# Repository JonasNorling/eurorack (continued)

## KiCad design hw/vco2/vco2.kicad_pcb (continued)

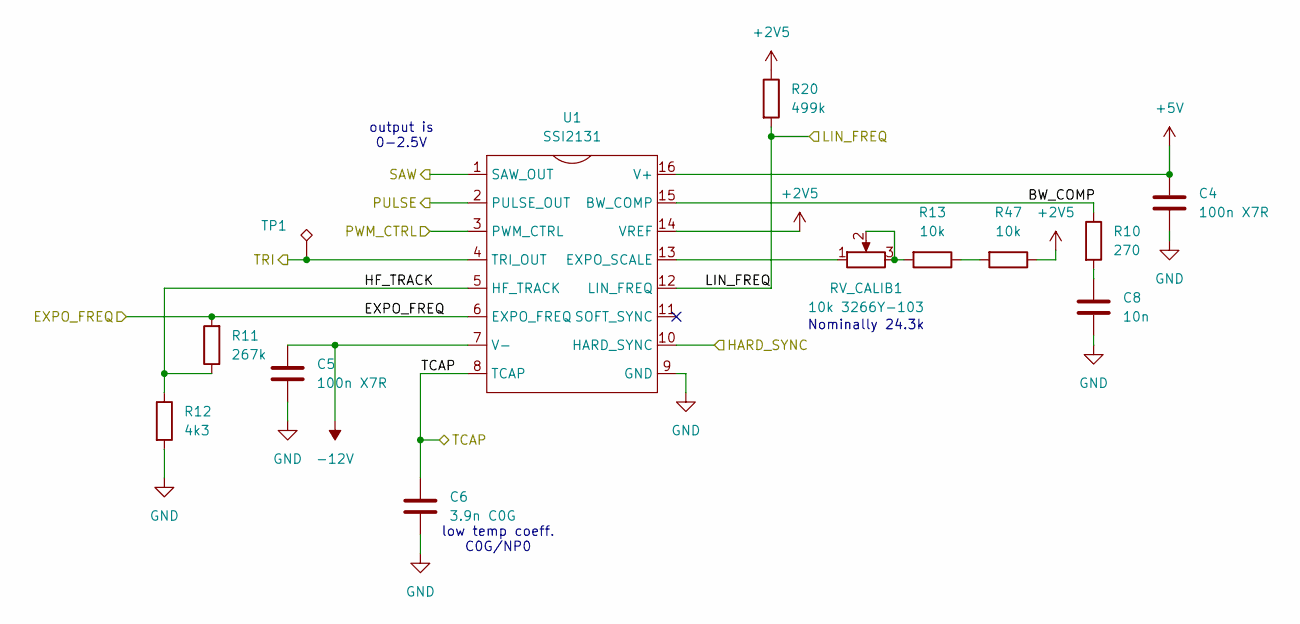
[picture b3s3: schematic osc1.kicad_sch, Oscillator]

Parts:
C4, C5: 100n X7R; C_0603_1608Metric
C6: 3.9n C0G; C_0603_1608Metric
C8: 10n; C_0603_1608Metric
R10: 270; R_0603_1608Metric
R11: 267k; R_0603_1608Metric
R12: 4k3; R_0603_1608Metric
R13, R47: 10k; R_0603_1608Metric
R20: 499k; R_0603_1608Metric
RV_CALIB1: 10k 3266Y-103; Potentiometer_Bourns_3266Y_Vertical
TP1: TestPoint_Alt; TP_0.9mm
U1: SSI2131; STC_SOP-16_3.9x9.9mm_P1.27mm; LCSC C9900051822

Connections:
+2V5: R20.1, R47.1, U1.14 (VREF); also elsewhere on the board
+5V: C4.1, U1.16 (V+); also elsewhere on the board
-12V: C5.1, U1.7 (V-); also elsewhere on the board
/EXPO_FREQ1: R11.2, U1.6 (EXPO_FREQ); also elsewhere on the board
/HARD_SYNC1: U1.10 (HARD_SYNC); also elsewhere on the board
/LIN_FREQ1: R20.2, U1.12 (LIN_FREQ); also elsewhere on the board
/Oscillator 1/BW_COMP: R10.1, U1.15 (BW_COMP)
/Oscillator 1/HF_TRACK: R11.1, R12.1, U1.5 (HF_TRACK)
/Oscillator 1/TCAP: C6.1, U1.8 (TCAP)
/PULSE1: U1.2 (PULSE_OUT); also elsewhere on the board
/PWM_CTRL1: U1.3 (PWM_CTRL); also elsewhere on the board
/SAW1: U1.1 (SAW_OUT); also elsewhere on the board
/TRI1: TP1.1, U1.4 (TRI_OUT); also elsewhere on the board
GND: C4.2, C5.2, C6.2, C8.2, R12.2, U1.9 (GND); also elsewhere on the board
unnamed: C8.1, R10.2
unnamed: R13.1, R47.2
unnamed: R13.2, RV_CALIB1.2, RV_CALIB1.3
unnamed: RV_CALIB1.1, U1.13 (EXPO_SCALE)

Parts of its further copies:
C24, C27: 100n X7R; C_0603_1608Metric
C25: 3.9n C0G; C_0603_1608Metric
C26: 10n; C_0603_1608Metric
R48, R66: 10k; R_0603_1608Metric
R63: 4k3; R_0603_1608Metric
R64: 267k; R_0603_1608Metric
R65: 499k; R_0603_1608Metric
R67: 270; R_0603_1608Metric
RV_CALIB2: 10k 3266Y-103; Potentiometer_Bourns_3266Y_Vertical
TP9: TestPoint_Alt; TP_0.9mm
U9: SSI2131; STC_SOP-16_3.9x9.9mm_P1.27mm; LCSC C9900051822

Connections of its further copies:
+2V5: R48.1, R65.1, U9.14 (VREF); also elsewhere on the board
+5V: C27.1, U9.16 (V+); also elsewhere on the board
-12V: C24.1, U9.7 (V-); also elsewhere on the board
/EXPO_FREQ2: R64.2, U9.6 (EXPO_FREQ); also elsewhere on the board
/HARD_SYNC2: U9.10 (HARD_SYNC); also elsewhere on the board
/Oscillator 2/BW_COMP: R67.1, U9.15 (BW_COMP)
/Oscillator 2/HF_TRACK: R63.1, R64.1, U9.5 (HF_TRACK)
/Oscillator 2/LIN_FREQ: R65.2, U9.12 (LIN_FREQ)
/PULSE2: U9.2 (PULSE_OUT); also elsewhere on the board
/PWM_CTRL2: U9.3 (PWM_CTRL); also elsewhere on the board
/SAW2: U9.1 (SAW_OUT); also elsewhere on the board
/TCAP2: C25.1, U9.8 (TCAP); also elsewhere on the board
/TRI2: TP9.1, U9.4 (TRI_OUT); also elsewhere on the board
GND: C24.2, C25.2, C26.2, C27.2, R63.2, U9.9 (GND); also elsewhere on the board
unnamed: C26.1, R67.2
unnamed: R48.2, R66.1
unnamed: R66.2, RV_CALIB2.2, RV_CALIB2.3
unnamed: RV_CALIB2.1, U9.13 (EXPO_SCALE)

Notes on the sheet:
Nominally 24.3k
low temp coeff. C0G/NP0
output is 0-2.5V

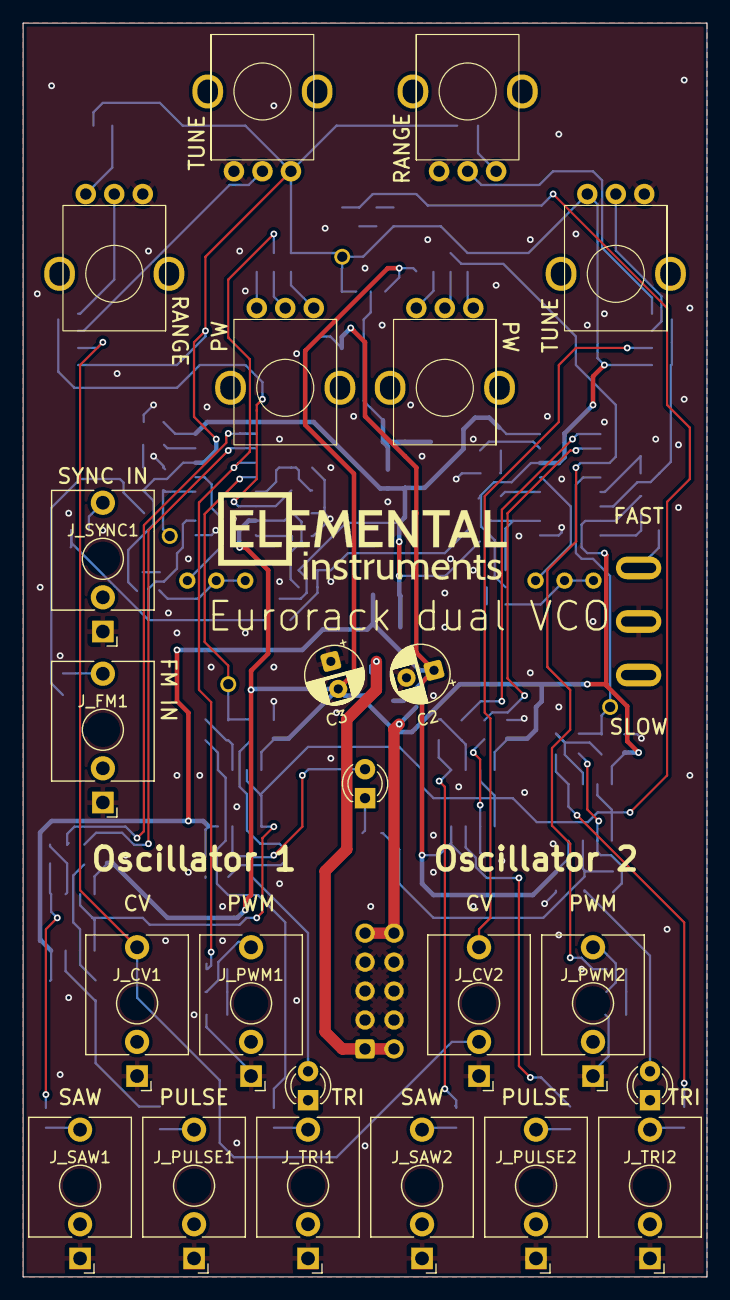
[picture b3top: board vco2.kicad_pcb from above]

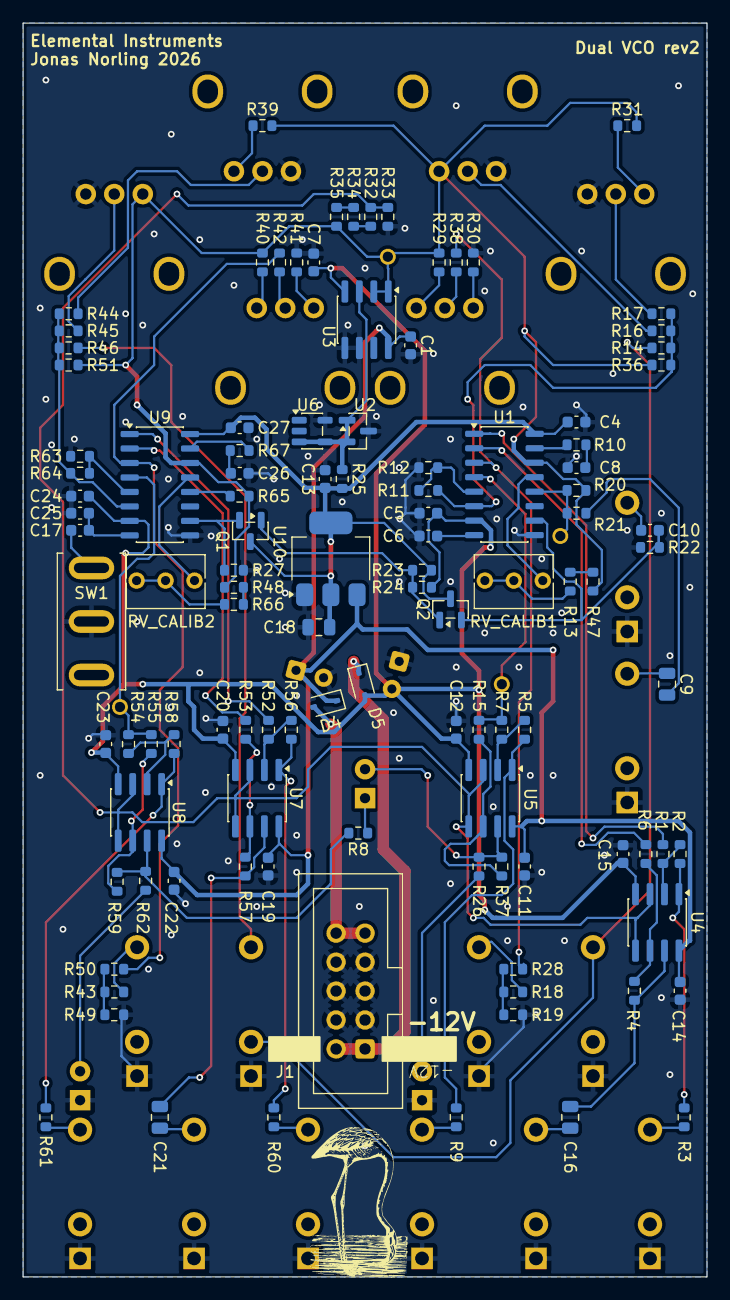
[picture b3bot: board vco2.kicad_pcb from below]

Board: 2 copper layers, 60.0 x 110.0 mm, 137 parts (114 on the bottom side), 87 nets.

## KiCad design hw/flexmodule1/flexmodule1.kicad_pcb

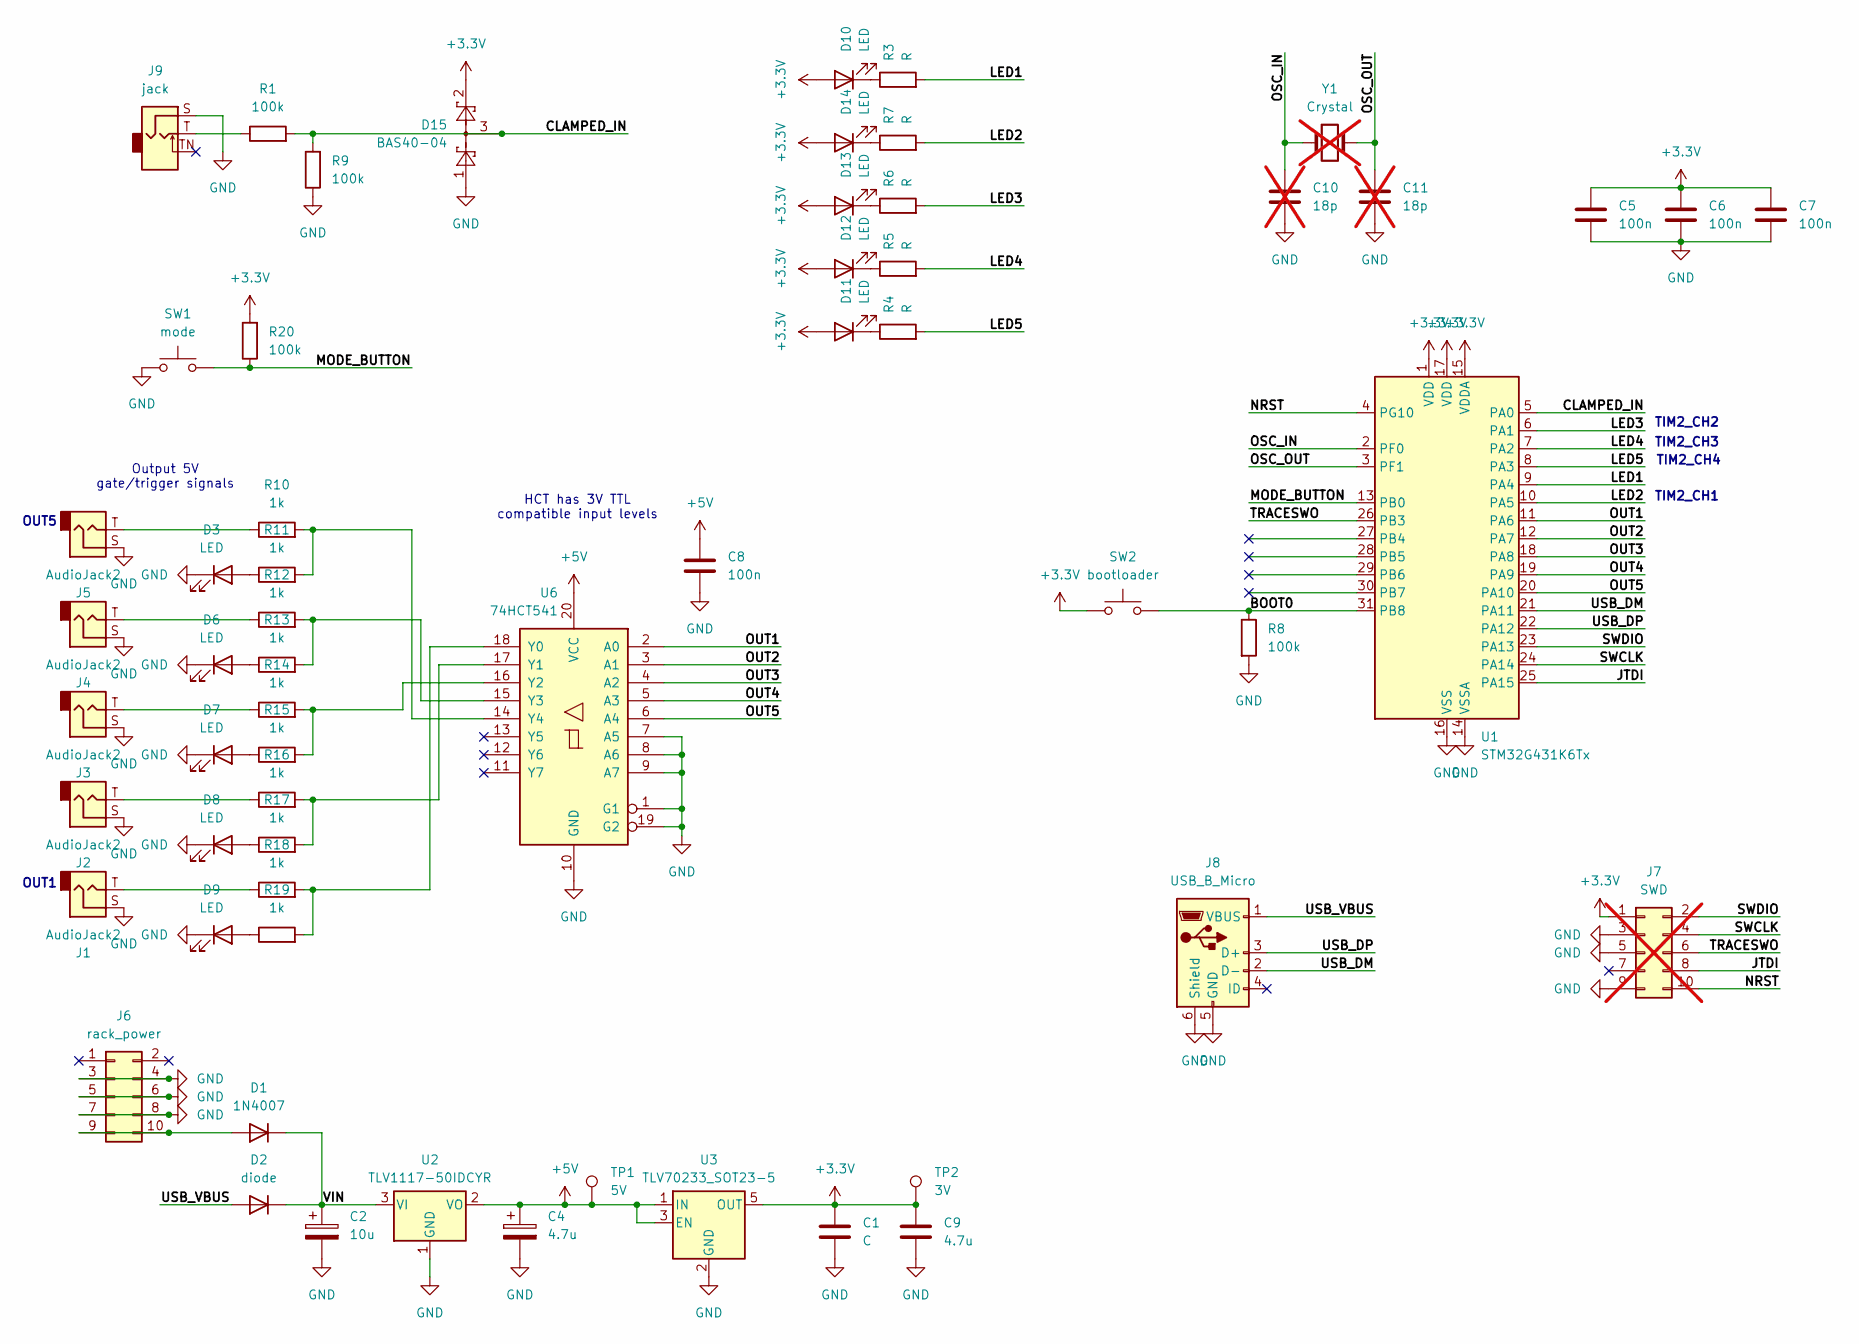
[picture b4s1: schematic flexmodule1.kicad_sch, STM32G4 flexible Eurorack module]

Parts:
C1: C; C_0603_1608Metric_Pad1.08x0.95mm_HandSolder
C2: 10u; CP_Radial_D5.0mm_P2.50mm
C4, C9: 4.7u; C_1206_3216Metric_Pad1.33x1.80mm_HandSolder
C5, C6, C7, C8: 100n; C_0603_1608Metric_Pad1.08x0.95mm_HandSolder
C10, C11: 18p; C_0603_1608Metric_Pad1.08x0.95mm_HandSolder; not fitted
D1: 1N4007; D_SOD-323
D2: diode; D_SOD-323
D3, D6, D7, D8, D9, D10, D11, D12, D13, D14: LED; LED_D3.0mm
D15: BAS40-04; SOT-23
J1, J2, J3, J4, J5: AudioJack2; Jack_3.5mm_QingPu_WQP-PJ398SM_Vertical_CircularHoles
J6: rack_power; IDC-Header_2x05_P2.54mm_Vertical
J7: SWD; PinHeader_2x05_P1.27mm_Vertical; not fitted
J8: USB_B_Micro; USB_Micro-B_Amphenol_10118193-0001LF_Horizontal
J9: jack; Jack_3.5mm_QingPu_WQP-PJ398SM_Vertical_CircularHoles
R1, R8, R9, R20: 100k; R_0603_1608Metric_Pad0.98x0.95mm_HandSolder
R3, R4, R5, R6, R7: R; R_0603_1608Metric_Pad0.98x0.95mm_HandSolder
R10, R11, R12, R13, R14, R15, R16, R17, R18, R19: 1k; R_0603_1608Metric_Pad0.98x0.95mm_HandSolder
SW1: mode; SW_PUSH-12mm
SW2: bootloader; SW_SPST_B3S-1000
TP1: 5V; TP_0.9mm
TP2: 3V; TP_0.9mm
U1: STM32G431K6Tx; LQFP-32_7x7mm_P0.8mm
U2: TLV1117-50IDCYR; SOT-223-3_TabPin2
U3: TLV70233_SOT23-5; SOT-23-5
U6: 74HCT541; TSSOP-20_4.4x6.5mm_P0.65mm
Y1: Crystal; Crystal_HC49-U_Vertical; not fitted

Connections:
+3.3V: C1.1, C5.1, C6.1, C7.1, C9.1, D10.2 (A), D11.2 (A), D12.2 (A), D13.2 (A), D14.2 (A), D15.2, J7.1, R20.2, SW2.1, TP2.1, U1.1 (VDD), U1.15 (VDDA), U1.17 (VDD), U3.5 (OUT)
+5V: C4.1, C8.1, TP1.1, U2.2 (VO), U3.1 (IN), U3.3 (EN), U6.20 (VCC)
/BOOT0: R8.1, SW2.2, U1.31 (PB8)
/CLAMPED_IN: D15.3, R1.2, R9.2, U1.5 (PA0)
/JTDI: J7.8, U1.25 (PA15)
/LED1: R3.2, U1.9 (PA4)
/LED2: R7.2, U1.10 (PA5)
/LED3: R6.2, U1.6 (PA1)
/LED4: R5.2, U1.7 (PA2)
/LED5: R4.2, U1.8 (PA3)
/MODE_BUTTON: R20.1, SW1.2, U1.13 (PB0)
/NRST: J7.10, U1.4 (PG10)
/OSC_IN: C10.1, U1.2 (PF0), Y1.1
/OSC_OUT: C11.1, U1.3 (PF1), Y1.2
/OUT1: U1.11 (PA6), U6.2 (A0)
/OUT2: U1.12 (PA7), U6.3 (A1)
/OUT3: U1.18 (PA8), U6.4 (A2)
/OUT4: U1.19 (PA9), U6.5 (A3)
/OUT5: U1.20 (PA10), U6.6 (A4)
/SWCLK: J7.4, U1.24 (PA14)
/SWDIO: J7.2, U1.23 (PA13)
/TRACESWO: J7.6, U1.26 (PB3)
/USB_DM: J8.2 (D-), U1.21 (PA11)
/USB_DP: J8.3 (D+), U1.22 (PA12)
/USB_VBUS: D2.2 (A), J8.1 (VBUS)
/VIN: C2.1, D1.1 (K), D2.1 (K), U2.3 (VI)
GND: C1.2, C2.2, C4.2, C5.2, C6.2, C7.2, C8.2, C9.2, C10.2, C11.2, D3.1 (K), D6.1 (K), D7.1 (K), D8.1 (K), D9.1 (K), D15.1, J1.S, J2.S, J3.S, J4.S, J5.S, J6.3, J6.4, J6.5, J6.6, J6.7, J6.8, J7.3, J7.5, J7.9, J8.5 (GND), J8.6 (Shield), J9.S, R8.2, R9.1, SW1.1, U1.14 (VSSA), U1.16 (VSS), U1.32 (VSS), U2.1 (GND), U3.2 (GND), U6.1 (G1), U6.7 (A5), U6.8 (A6), U6.9 (A7), U6.10 (GND), U6.19 (G2)
unnamed: D1.2 (A), J6.9, J6.10
unnamed: D3.2 (A), R11.1
unnamed: D6.2 (A), R13.1
unnamed: D7.2 (A), R15.1
unnamed: D8.2 (A), R17.1
unnamed: D9.2 (A), R19.1
unnamed: D10.1 (K), R3.1
unnamed: D11.1 (K), R4.1
unnamed: D12.1 (K), R5.1
unnamed: D13.1 (K), R6.1
unnamed: D14.1 (K), R7.1
unnamed: J1.T, R18.1
unnamed: J2.T, R16.1
unnamed: J3.T, R14.1
unnamed: J4.T, R12.1
unnamed: J5.T, R10.1
unnamed: J9.T, R1.1
unnamed: R18.2, R19.2, U6.18 (Y0)
unnamed: R16.2, R17.2, U6.17 (Y1)
unnamed: R14.2, R15.2, U6.16 (Y2)
unnamed: R12.2, R13.2, U6.15 (Y3)
unnamed: R10.2, R11.2, U6.14 (Y4)

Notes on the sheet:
OUT1
TIM2_CH4
OUT5
TIM2_CH3
TIM2_CH1
HCT has 3V TTL compatible input levels
Output 5V gate/trigger signals
TIM2_CH2

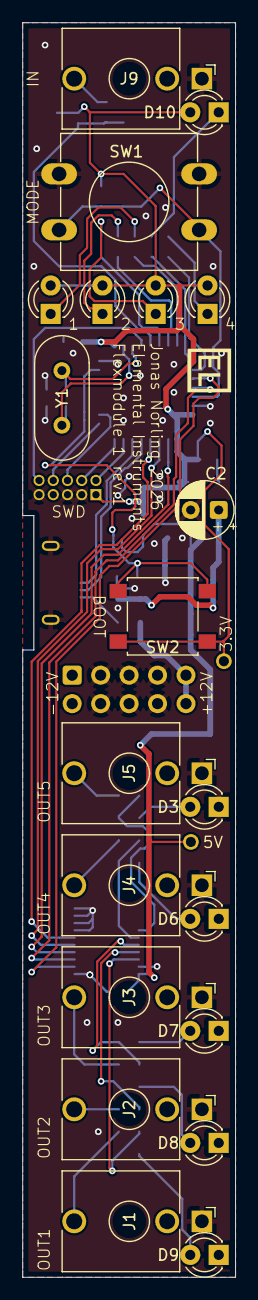
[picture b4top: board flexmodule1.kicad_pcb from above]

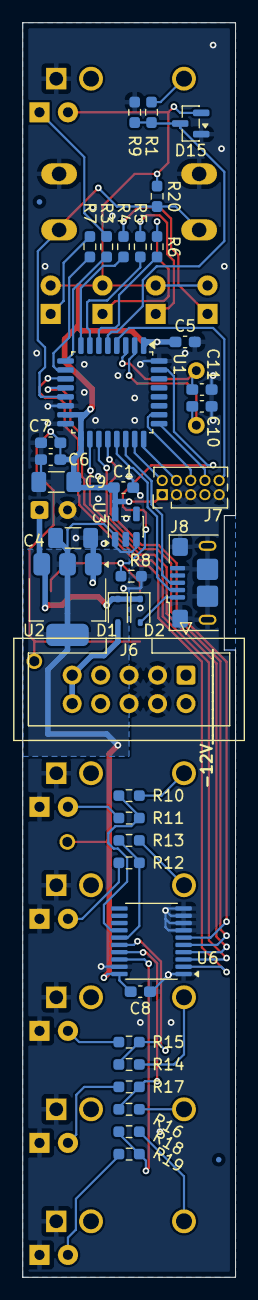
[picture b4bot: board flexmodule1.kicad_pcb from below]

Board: 2 copper layers, 19.0 x 112.0 mm, 60 parts (38 on the bottom side), 49 nets.

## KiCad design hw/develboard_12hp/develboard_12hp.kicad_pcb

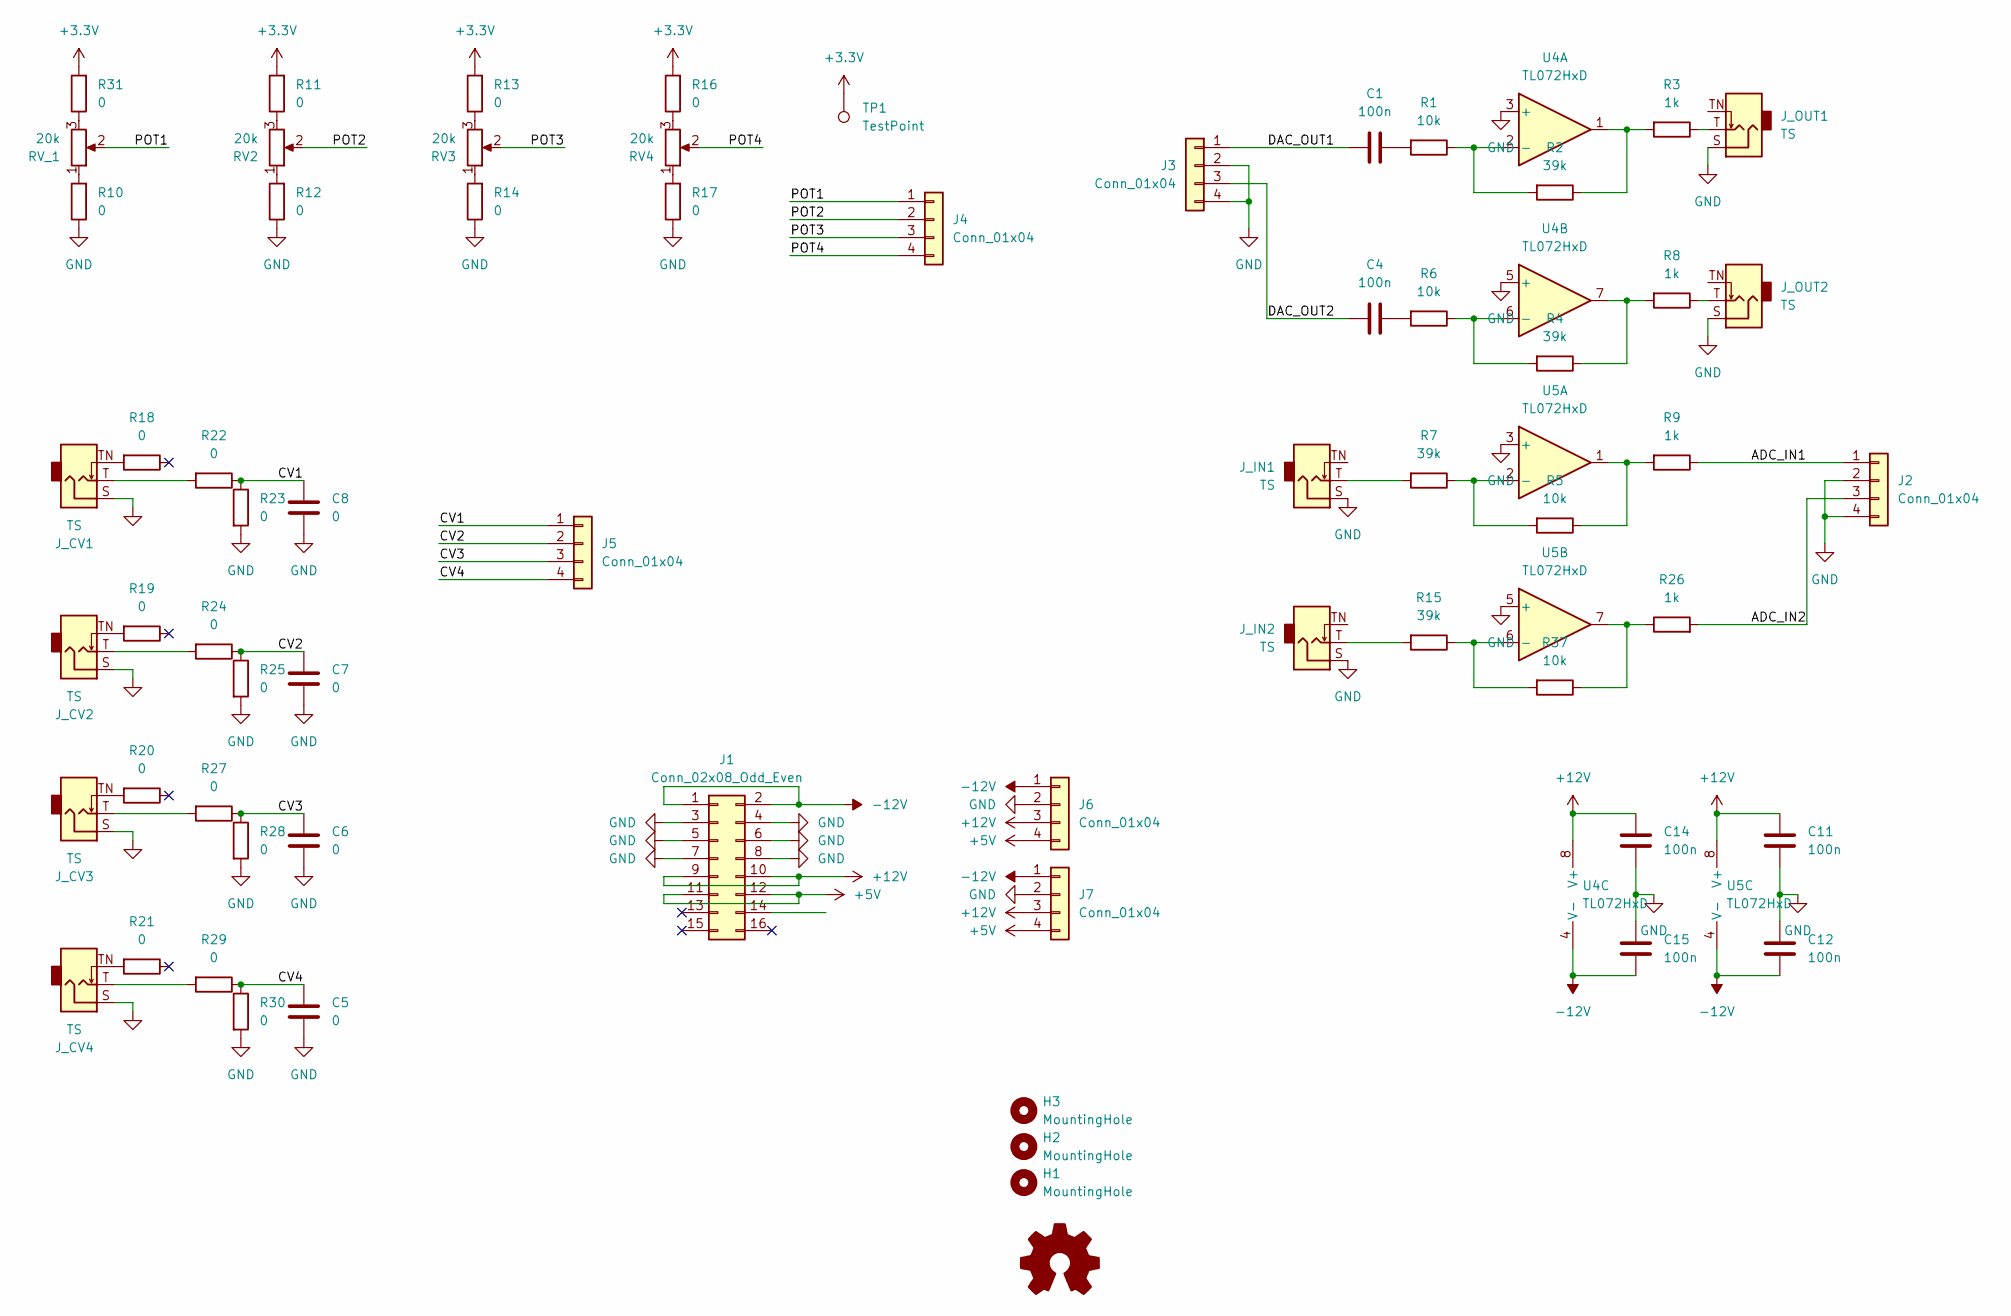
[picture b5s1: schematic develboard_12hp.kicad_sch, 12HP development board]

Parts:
C1, C4: 100n; C_0805_2012Metric_Pad1.18x1.45mm_HandSolder
C5, C6, C7, C8: 0; C_0603_1608Metric_Pad1.08x0.95mm_HandSolder
C11, C12, C14, C15: 100n; C_0603_1608Metric_Pad1.08x0.95mm_HandSolder
H1, H2, H3: MountingHole; MountingHole_3.2mm_M3_Pad
J1: Conn_02x08_Odd_Even; IDC-Header_2x08_P2.54mm_Vertical
J2, J3, J4, J5, J6, J7: Conn_01x04; PinHeader_1x04_P2.54mm_Vertical
J_CV1, J_CV2, J_CV3, J_CV4: TS; Jack_3.5mm_QingPu_WQP-PJ398SM_Vertical_CircularHoles
J_IN1, J_IN2: TS; Jack_3.5mm_QingPu_WQP-PJ398SM_Vertical_CircularHoles
J_OUT1, J_OUT2: TS; Jack_3.5mm_QingPu_WQP-PJ398SM_Vertical_CircularHoles
R1, R5, R6, R37: 10k; R_0603_1608Metric_Pad0.98x0.95mm_HandSolder
R2, R4, R7, R15: 39k; R_0603_1608Metric_Pad0.98x0.95mm_HandSolder
R3, R8, R9, R26: 1k; R_0603_1608Metric_Pad0.98x0.95mm_HandSolder
R10, R11, R12, R13, R14, R16, R17, R18, R19, R20, R21, R22, R23, R24, R25, R27, R28, R29, R30, R31: 0; R_0603_1608Metric_Pad0.98x0.95mm_HandSolder
RV2, RV3, RV4: 20k; RV9012NO
RV_1: 20k; RV9012NO
TP1: TestPoint; TP_0.9mm
U4, U5: TL072HxD; SOIC-8_3.9x4.9mm_P1.27mm

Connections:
+3.3V: R11.2, R13.2, R16.2, R31.2, TP1.1
+5V: J1.11, J1.12, J6.4, J7.4
+12V: C11.1, C14.1, J1.9, J1.10, J6.3, J7.3, U4.8 (V+), U5.8 (V+)
-12V: C12.2, C15.2, J1.1, J1.2, J6.1, J7.1, U4.4 (V-), U5.4 (V-)
/ADC_IN1: J2.1, R9.1
/ADC_IN2: J2.3, R26.2
/CV1: C8.1, J5.1, R22.1, R23.1
/CV2: C7.1, J5.2, R24.1, R25.1
/CV3: C6.1, J5.3, R27.1, R28.1
/CV4: C5.1, J5.4, R29.1, R30.1
/DAC_OUT1: C1.1, J3.1
/DAC_OUT2: C4.1, J3.3
/POT1: J4.1, RV_1.2
/POT2: J4.2, RV2.2
/POT3: J4.3, RV3.2
/POT4: J4.4, RV4.2
GND: C5.2, C6.2, C7.2, C8.2, C11.2, C12.1, C14.2, C15.1, J1.3, J1.4, J1.5, J1.6, J1.7, J1.8, J2.2, J2.4, J3.2, J3.4, J6.2, J7.2, J_CV1.S, J_CV2.S, J_CV3.S, J_CV4.S, J_IN1.S, J_IN2.S, J_OUT1.S, J_OUT2.S, R10.1, R12.1, R14.1, R17.1, R23.2, R25.2, R28.2, R30.2, U4.3 (+), U4.5 (+), U5.3 (+), U5.5 (+)
unnamed: C1.2, R1.2
unnamed: C4.2, R6.2
unnamed: J_CV1.T, R22.2
unnamed: J_CV1.TN, R18.2
unnamed: J_CV2.T, R24.2
unnamed: J_CV2.TN, R19.2
unnamed: J_CV3.T, R27.2
unnamed: J_CV3.TN, R20.2
unnamed: J_CV4.T, R29.2
unnamed: J_CV4.TN, R21.2
unnamed: J_IN1.T, R7.2
unnamed: J_IN2.T, R15.2
unnamed: J_OUT1.T, R3.1
unnamed: J_OUT2.T, R8.1
unnamed: R2.1, R3.2, U4.1
unnamed: R4.1, R8.2, U4.7
unnamed: R5.1, R9.2, U5.1
unnamed: R10.2, RV_1.1
unnamed: R11.1, RV2.3
unnamed: R12.2, RV2.1
unnamed: R13.1, RV3.3
unnamed: R14.2, RV3.1
unnamed: R16.1, RV4.3
unnamed: R17.2, RV4.1
unnamed: R26.1, R37.1, U5.7
unnamed: R31.1, RV_1.3
unnamed: R1.1, R2.2, U4.2 (-)
unnamed: R4.2, R6.1, U4.6 (-)
unnamed: R5.2, R7.1, U5.2 (-)
unnamed: R15.1, R37.2, U5.6 (-)

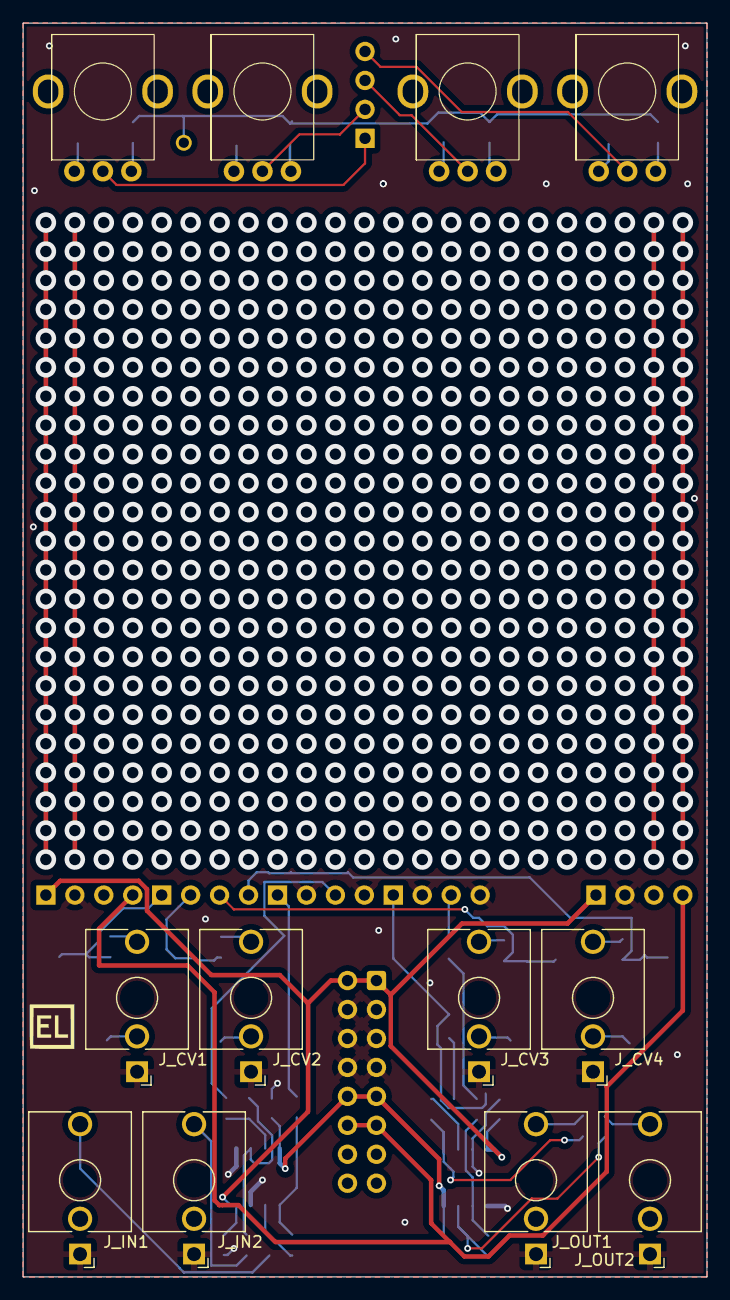
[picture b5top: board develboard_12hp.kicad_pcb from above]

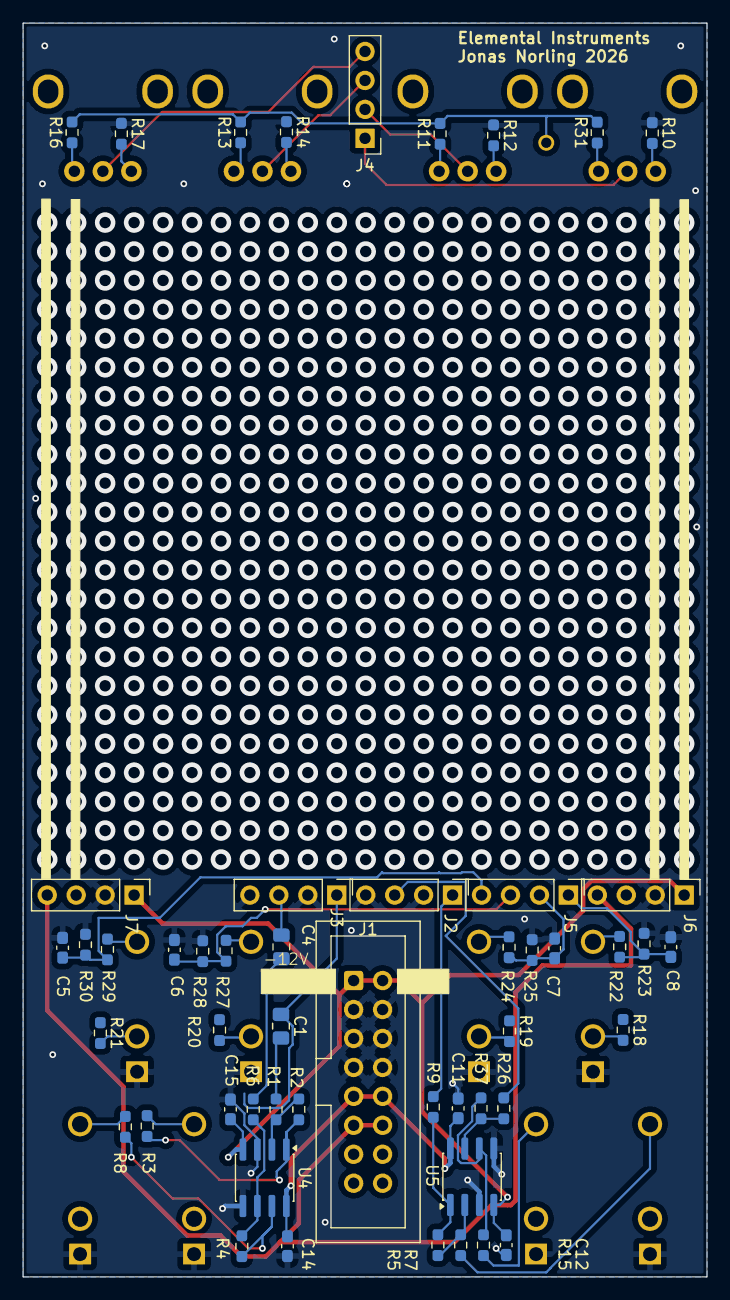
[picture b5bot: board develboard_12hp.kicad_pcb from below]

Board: 2 copper layers, 60.0 x 110.0 mm, 64 parts (51 on the bottom side), 47 nets.

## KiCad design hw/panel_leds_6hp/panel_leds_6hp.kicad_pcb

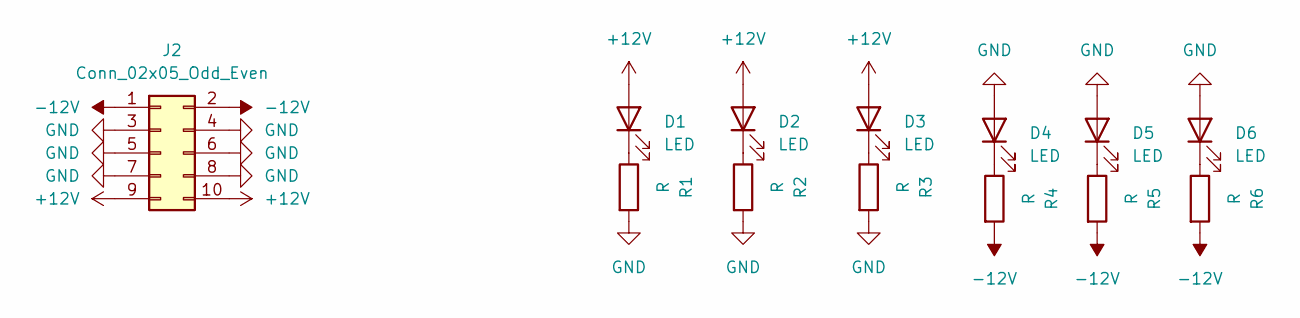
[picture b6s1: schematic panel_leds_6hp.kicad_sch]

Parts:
D1, D2, D3, D4, D5, D6: LED; LED 1206 reverse mount with hole
J2: Conn_02x05_Odd_Even; PinHeader_2x05_P2.54mm_Vertical_SMD
R1, R2, R3, R4, R5, R6: R; R_0603_1608Metric_Pad0.98x0.95mm_HandSolder

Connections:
+12V: D1.2 (A), D2.2 (A), D3.2 (A), J2.9, J2.10
-12V: J2.1, J2.2, R4.2, R5.2, R6.2
GND: D4.2 (A), D5.2 (A), D6.2 (A), J2.3, J2.4, J2.5, J2.6, J2.7, J2.8, R1.2, R2.2, R3.2
unnamed: D1.1 (K), R1.1
unnamed: D2.1 (K), R2.1
unnamed: D3.1 (K), R3.1
unnamed: D4.1 (K), R4.1
unnamed: D5.1 (K), R5.1
unnamed: D6.1 (K), R6.1

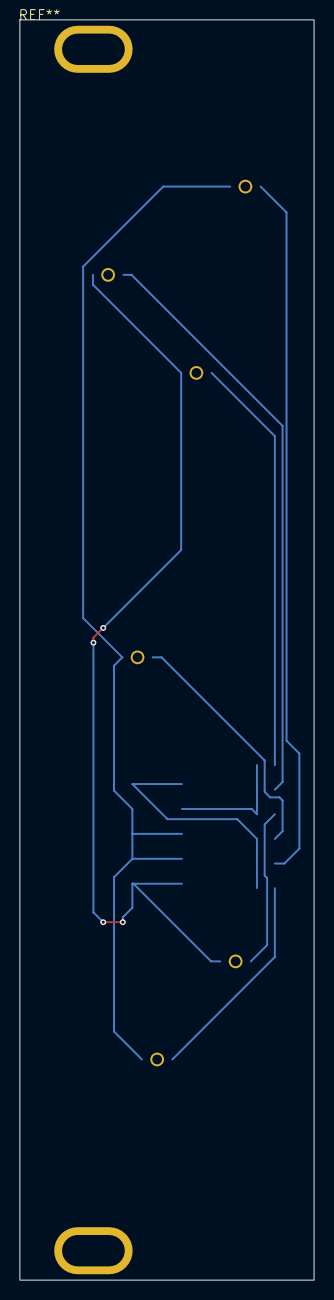
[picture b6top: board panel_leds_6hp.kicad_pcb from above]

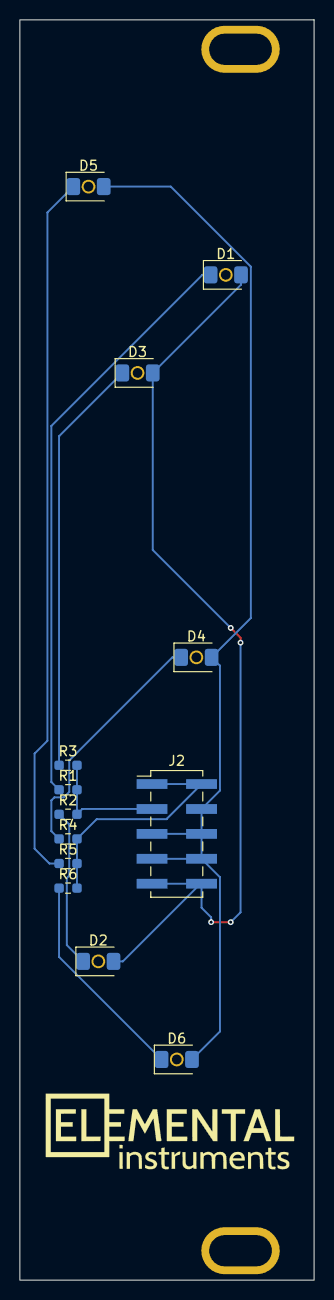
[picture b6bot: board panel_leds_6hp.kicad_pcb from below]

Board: 2 copper layers, 30.0 x 128.5 mm, 13 parts (13 on the bottom side), 9 nets.

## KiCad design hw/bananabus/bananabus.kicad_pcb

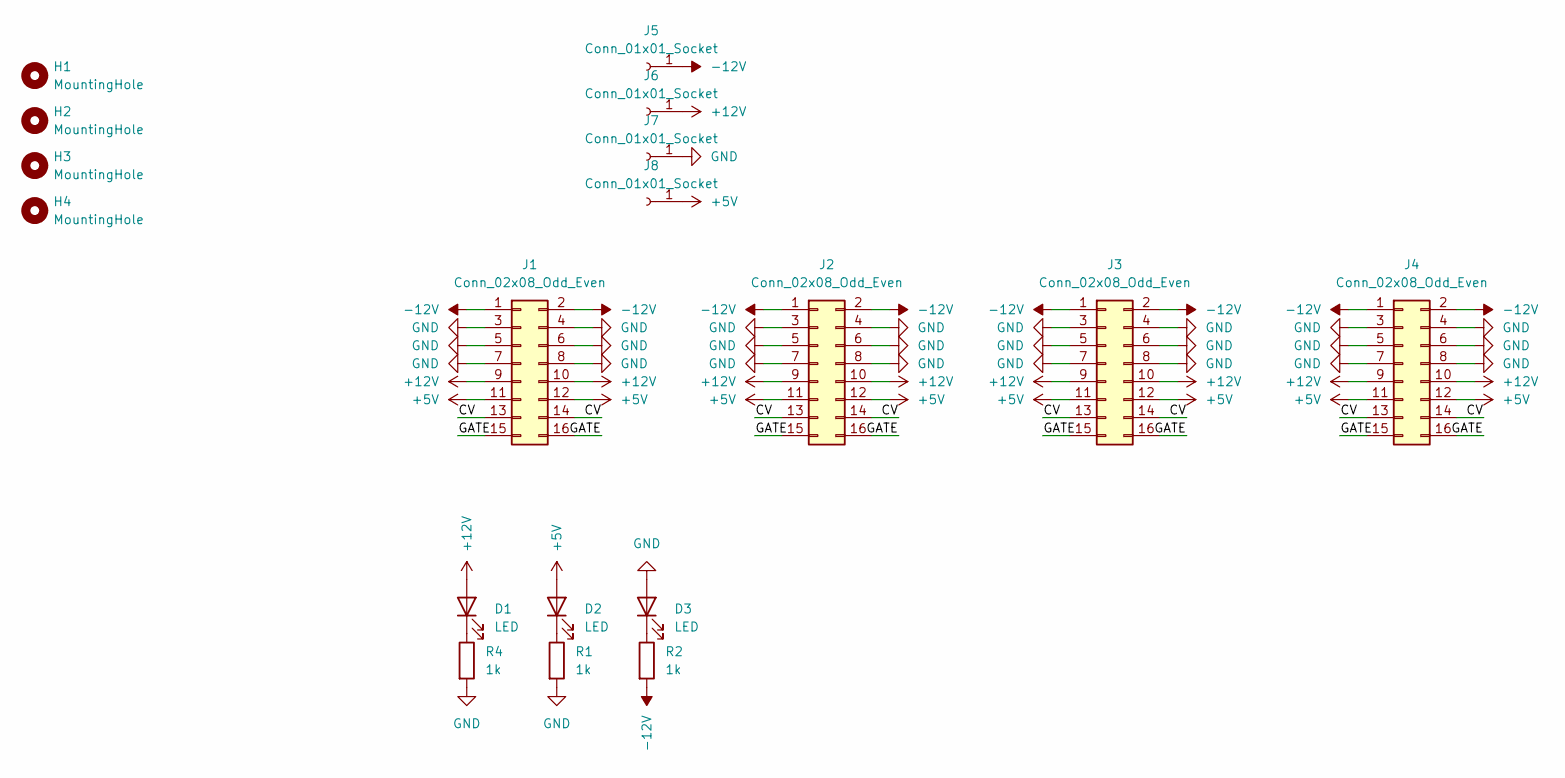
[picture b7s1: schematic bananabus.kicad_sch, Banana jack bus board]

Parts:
D1, D2, D3: LED; LED_0805_2012Metric_Pad1.15x1.40mm_HandSolder
H1, H2, H3, H4: MountingHole; MountingHole_3.2mm_M3_Pad
J1, J2, J3, J4: Conn_02x08_Odd_Even; IDC-Header_2x08_P2.54mm_Vertical
J5, J6, J7, J8: Conn_01x01_Socket; Multicomp Banana jack
R1, R2, R4: 1k; R_0603_1608Metric_Pad0.98x0.95mm_HandSolder

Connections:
+5V: D2.2 (A), J1.11, J1.12, J2.11, J2.12, J3.11, J3.12, J4.11, J4.12, J8.1
+12V: D1.2 (A), J1.9, J1.10, J2.9, J2.10, J3.9, J3.10, J4.9, J4.10, J6.1
-12V: J1.1, J1.2, J2.1, J2.2, J3.1, J3.2, J4.1, J4.2, J5.1, R2.2
/CV: J1.13, J1.14, J2.13, J2.14, J3.13, J3.14, J4.13, J4.14
/GATE: J1.15, J1.16, J2.15, J2.16, J3.15, J3.16, J4.15, J4.16
GND: D3.2 (A), J1.3, J1.4, J1.5, J1.6, J1.7, J1.8, J2.3, J2.4, J2.5, J2.6, J2.7, J2.8, J3.3, J3.4, J3.5, J3.6, J3.7, J3.8, J4.3, J4.4, J4.5, J4.6, J4.7, J4.8, J7.1, R1.2, R4.2
unnamed: D1.1 (K), R4.1
unnamed: D2.1 (K), R1.1
unnamed: D3.1 (K), R2.1

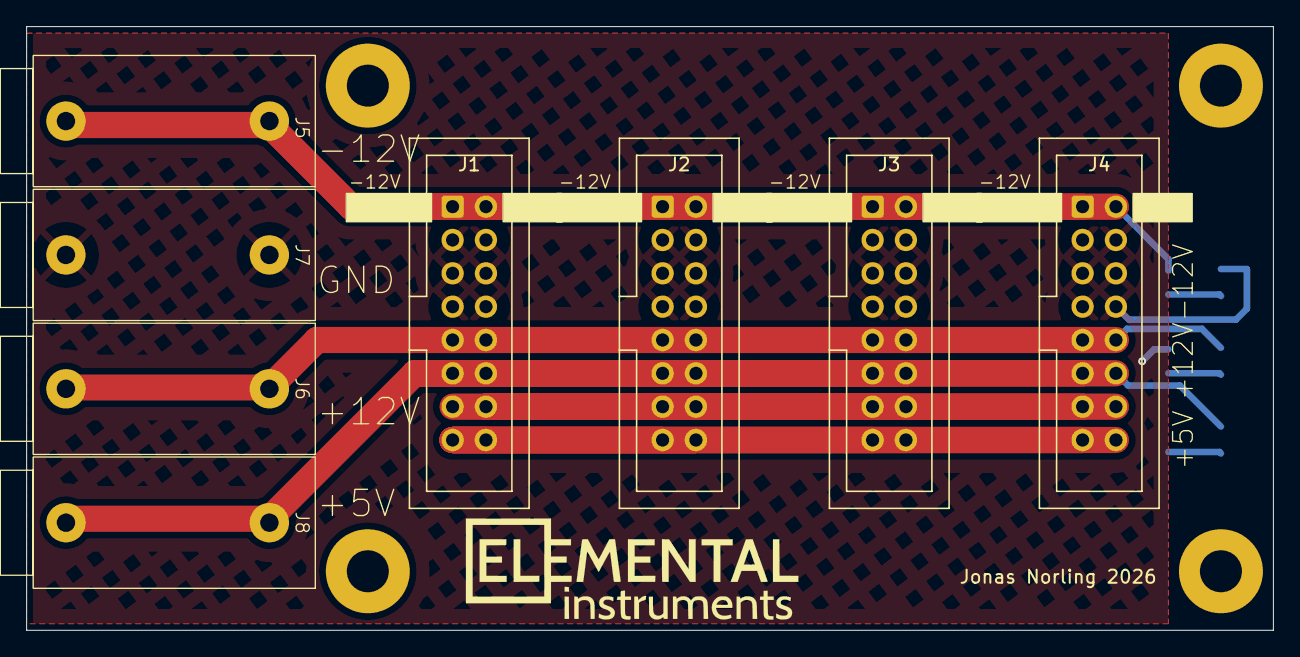
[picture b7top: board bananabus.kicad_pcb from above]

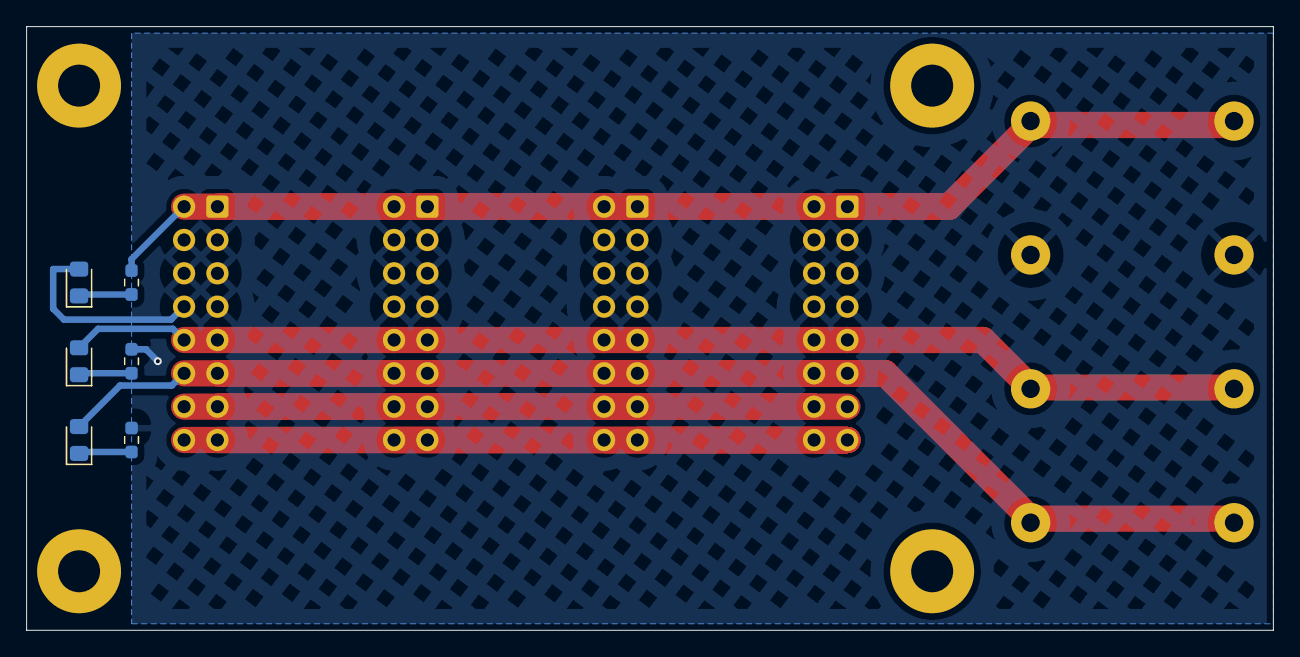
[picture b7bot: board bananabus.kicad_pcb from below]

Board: 2 copper layers, 95.0 x 46.0 mm, 18 parts (6 on the bottom side), 9 nets.

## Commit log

2026-01-25 Started VCO based on SSI2131
2026-01-26 Draw some more stuff
2026-01-30 Route most of the board
2026-01-31 More routing and stuff
2026-01-31 Fix footprints, add test points
2026-02-01 VCO prototype 1 to Aisler
2026-02-07 Move files
2026-02-15 As built, fixed a couple of issues
2026-02-15 Work on new dual VCO board
    Including fixes to vco1 prototype
2026-02-15 Dual VCO board
2026-02-16 Layout VCO2 board
2026-02-16 Place components
2026-02-16 Layout board
2026-02-17 Routing
2026-02-18 Banana jack bus board
2026-02-18 Banana bus gerbers
2026-02-18 Blind panel 4HP
2026-02-18 Blind panel 2 HP
2026-02-18 Blind panel 6 HP with LED "stars"
    Let's see what this looks like...
2026-02-18 Route board
2026-02-19 Clean up VCO board, reduce to 2 layers
2026-02-19 Add normalisation on outputs
2026-02-19 Outline for 12HP VCO2 front panel
2026-02-19 Blank panel for VCO2
2026-02-19 Tiny fixes to PCB layout
2026-02-19 VCO2 gerbers
2026-02-20 VCO2 panel
2026-02-20 Development board for fiddling for stuff
2026-02-21 Update VCO2 panel
2026-02-21 Stupid hurried development board
2026-03-01 WIP: STM32G4 digital module
2026-03-02 Change to a bigger LDO
    Use a bigger 5V regulator with 12V input tolerance, so it might be
    able to dissipate more heat. Not sure how warm this is going to get.
2026-03-14 WIP: Redesign VCO2 board
2026-03-14 WIP: VCO2 panel
2026-03-16 VCO2 production work
2026-04-04 VCO2 rev 2 as sent for production at JLCPCB
2026-04-06 Start work on Eurorack Brain Board, STM32G4 codec board
2026-04-08 Laying out brains board
2026-04-10 Maybe finished Brain board PCB
2026-04-10 Brainboard polishing
2026-04-11 More tiny adjustments
2026-04-11 Brainboard carrier board for testing
2026-04-11 Panel for brainboard
2026-04-11 Tiny adjustments
2026-04-11 More tiny adjustments. As ordered from JLCPCB.
2026-04-15 VCO2 rev 2 errata
